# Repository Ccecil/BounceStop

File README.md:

# BounceStop
Debounce interface with gadgeteer connections
Allows for hardware debouncing of signals with significant noise prevention.  Good for interfacing switches and other "slow" devices since the device has a built in delay/debounce.

Early prototype.  Not for production. Gadgeteer pinouts are not correct on 0.1 and 0.2 versions.  Will be corrected shortly.

0.2 version adds the pins for _CH and _EN which will allow a one shot trigger event when any pin is triggered...then you toggle to reset.  This allows the board to also be used as an 8:1 Interrupt expander or other functions

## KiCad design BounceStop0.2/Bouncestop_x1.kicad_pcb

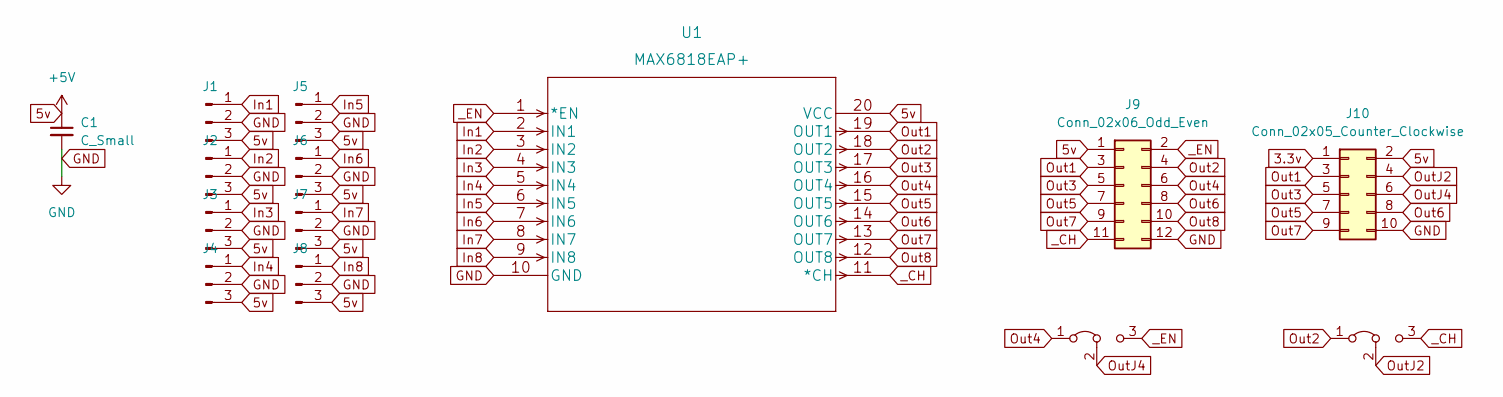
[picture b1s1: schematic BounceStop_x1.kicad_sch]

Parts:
C1: C_Small; C_0402_1005Metric
J1, J2, J3, J4, J5, J6, J7, J8: Conn_01x03_Male; Molex_KK-254_AE-6410-03A_1x03_P2.54mm_Vertical
J9: Conn_02x06_Odd_Even; PinHeader_1x12_P2.54mm_Vertical
J10: Conn_02x05_Counter_Clockwise; PinSocket_2x05_P1.27mm_Vertical_SMD
JP1, JP2: Jumper_3_Bridged12; SolderJumper-3_P1.3mm_Bridged12_RoundedPad1.0x1.5mm
U1: MAX6818EAP+; MAX6818EAP&plus_

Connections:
3.3v: J10.1
5v: C1.1, J1.3, J2.3, J3.3, J4.3, J5.3, J6.3, J7.3, J8.3, J9.1, J10.2, U1.20 (VCC)
GND: C1.2, J1.2, J2.2, J3.2, J4.2, J5.2, J6.2, J7.2, J8.2, J9.12, J10.10, U1.10 (GND)
In1: J1.1, U1.2 (IN1)
In2: J2.1, U1.3 (IN2)
In3: J3.1, U1.4 (IN3)
In4: J4.1, U1.5 (IN4)
In5: J5.1, U1.6 (IN5)
In6: J6.1, U1.7 (IN6)
In7: J7.1, U1.8 (IN7)
In8: J8.1, U1.9 (IN8)
Out1: J9.3, J10.3, U1.19 (OUT1)
Out2: J9.4, JP2.1 (A), U1.18 (OUT2)
Out3: J9.5, J10.5, U1.17 (OUT3)
Out4: J9.6, JP1.1 (A), U1.16 (OUT4)
Out5: J9.7, J10.7, U1.15 (OUT5)
Out6: J9.8, J10.8, U1.14 (OUT6)
Out7: J9.9, J10.9, U1.13 (OUT7)
Out8: J9.10, U1.12 (OUT8)
OutJ2: J10.4, JP2.2 (C)
OutJ4: J10.6, JP1.2 (C)
_CH: J9.11, JP2.3 (B), U1.11 (*CH)
_EN: J9.2, JP1.3 (B), U1.1 (*EN)

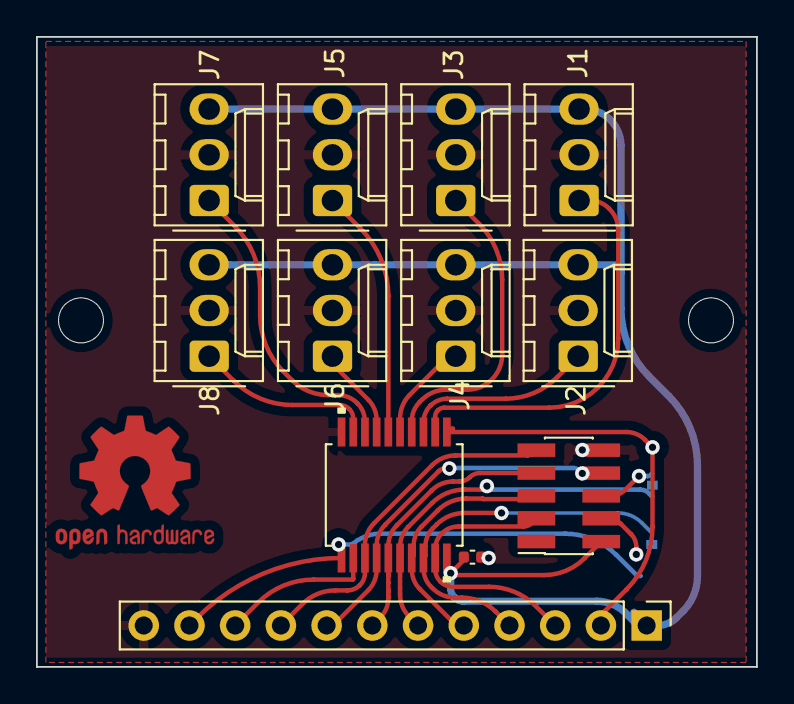
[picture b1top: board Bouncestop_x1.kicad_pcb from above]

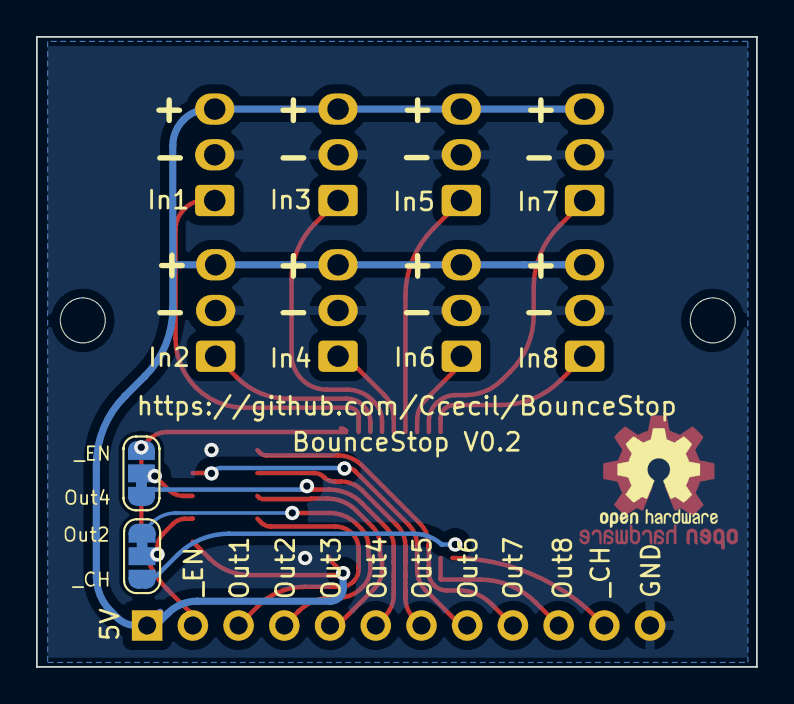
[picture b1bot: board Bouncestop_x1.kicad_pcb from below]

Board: 2 copper layers, 40.0 x 35.0 mm, 14 parts (2 on the bottom side), 22 nets.

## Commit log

2022-01-03 Initial upload
    Early prototype. Not intended for production.
2022-01-04 Initial Upload, Schematic, layout
2022-01-04 Add silk

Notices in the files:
parts and their libraries:
Copyright 2021 Accelerated Designs. All rights reserved.
